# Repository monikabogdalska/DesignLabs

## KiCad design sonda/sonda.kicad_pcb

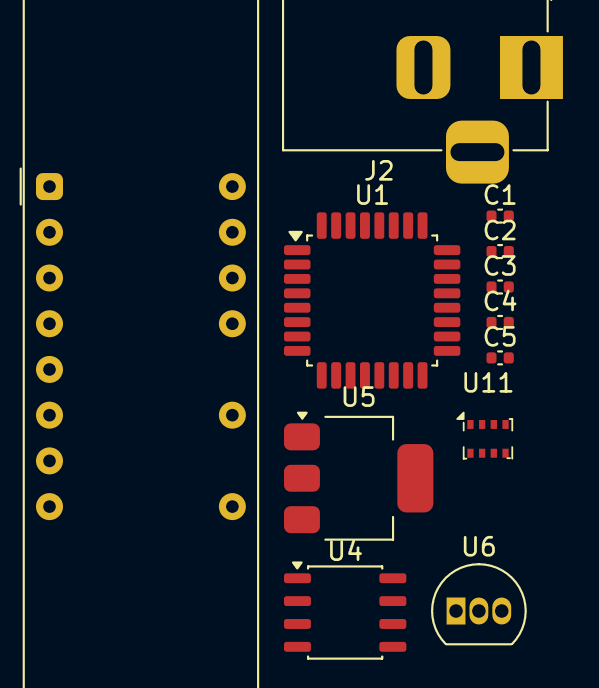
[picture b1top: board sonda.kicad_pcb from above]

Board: 2 copper layers, 12 parts (0 on the bottom side), 22 nets, no tracks yet.

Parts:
C1, C2, C3, C4, C5: 100nF; C_0402_1005Metric
J2: Jack-DC; BarrelJack_Horizontal
U1: ATmega328PB-A; TQFP-32_7x7mm_P0.8mm
U3: LTC-4627JD; LTC-4627Jx
U4: CH340N; JEITA_SOIC-8_3.9x4.9mm_P1.27mm
U5: AMS1117-3.3; SOT-223-3_TabPin2
U6: DS18B20; TO-92_Inline
U11: BMP280; Bosch_LGA-8_2x2.5mm_P0.65mm_ClockwisePinNumbering

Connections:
+3.3V: C1.1, C2.1, C4.1, C5.1, U1.4 (VCC), U3.1 (VCC), U4.5 (VCC), U5.2 (VO), U6.3 (V_{DD}), U11.8 (VDD)
+5V: C3.1, J2.1, U5.3 (VI)
GND: C1.2, C2.2, C3.2, C4.2, C5.2, J2.2, U1.5 (GND), U1.21 (GND), U4.3 (GND), U5.1 (GND), U6.1 (GND), U11.1 (GND), U11.7 (GND)
unnamed: U1.12 (PB0), U3.15 (G)
unnamed: U1.13 (PB1), U3.7 (DP)
unnamed: U1.14 (PB2), U11.2 (CSB)
unnamed: U1.15 (PB3), U11.5 (SDO)
unnamed: U1.16 (PB4), U11.3 (SDI)
unnamed: U1.17 (PB5), U11.4 (SCK)
unnamed: U1.23 (PC0), U3.2 (D1)
unnamed: U1.24 (PC1), U3.6 (D2)
unnamed: U1.25 (PC2), U3.8 (D3)
unnamed: U1.26 (PC3), U3.4 (D4)
unnamed: U1.30 (PD0), U4.6 (TXD)
unnamed: U1.31 (PD1), U4.7 (RXD)
unnamed: U1.32 (PD2), U6.2 (DQ)
unnamed: U1.1 (PD3), U3.16 (B)
unnamed: U1.2 (PD4), U3.13 (C)
unnamed: U1.9 (PD5), U3.3 (D)
unnamed: U1.10 (PD6), U3.5 (E)
unnamed: U1.11 (PD7), U3.11 (F)
unnamed: U1.7 (XTAL1/PB6), U3.14 (A)

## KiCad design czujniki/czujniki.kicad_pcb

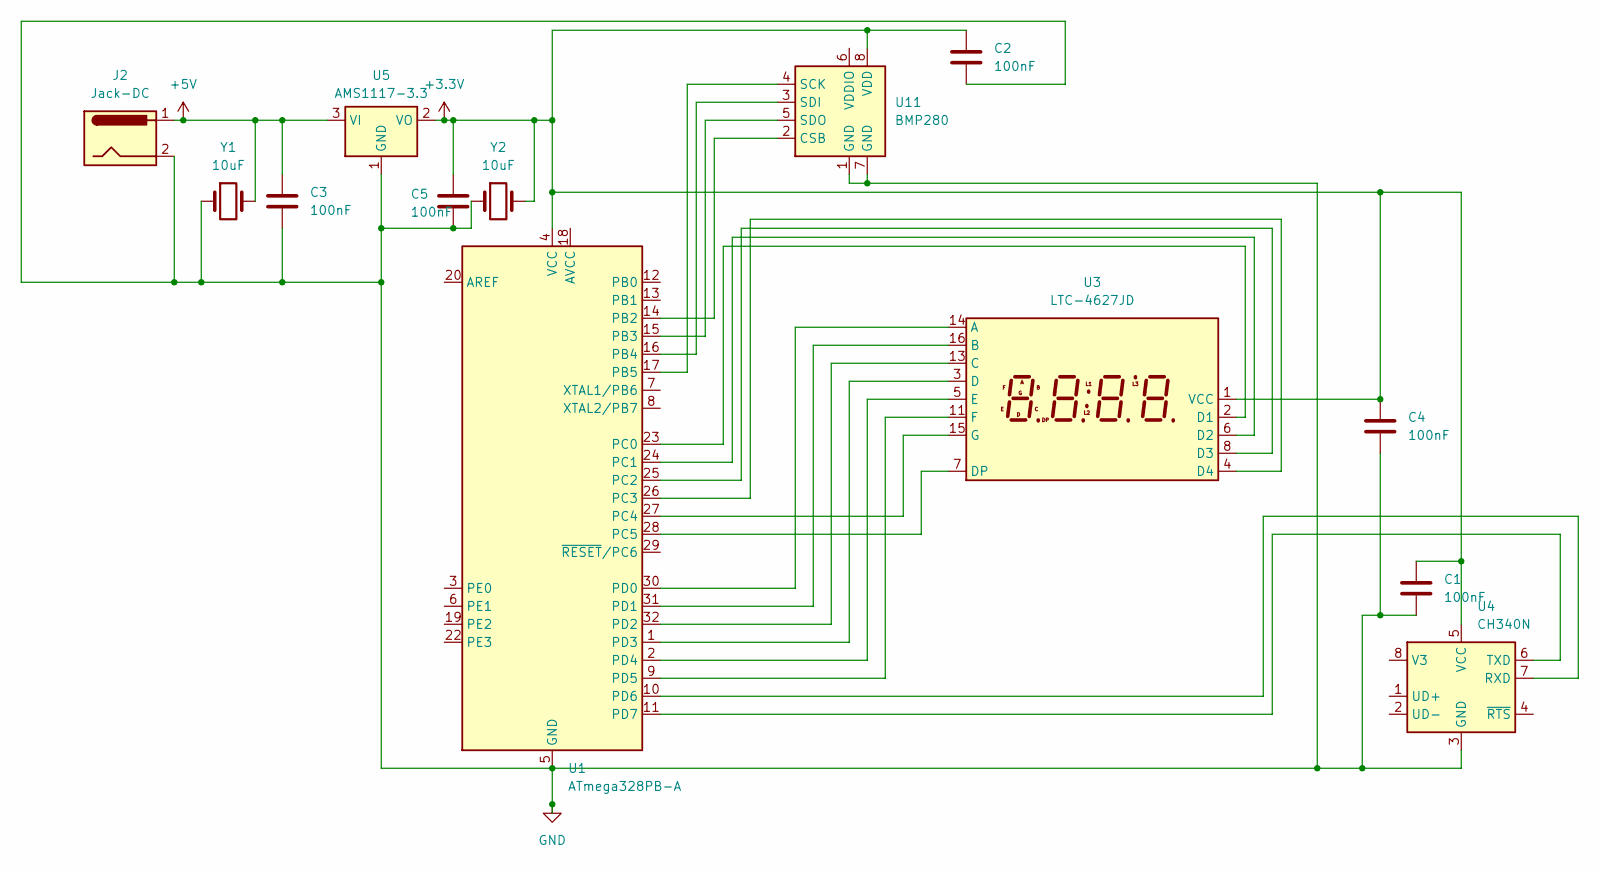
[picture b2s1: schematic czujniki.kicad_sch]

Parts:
C1, C2, C3, C4, C5: 100nF; C_0402_1005Metric
J2: Jack-DC; BarrelJack_Horizontal
U1: ATmega328PB-A; TQFP-32_7x7mm_P0.8mm
U3: LTC-4627JD; LTC-4627Jx
U4: CH340N; JEITA_SOIC-8_3.9x4.9mm_P1.27mm
U5: AMS1117-3.3; SOT-223-3_TabPin2
U11: BMP280; Bosch_LGA-8_2x2.5mm_P0.65mm_ClockwisePinNumbering
Y1, Y2: 10uF; CP_Elec_6.3x7.7

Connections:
+3.3V: C1.1, C2.1, C4.1, C5.1, U1.4 (VCC), U3.1 (VCC), U4.5 (VCC), U5.2 (VO), U11.8 (VDD), Y2.2
+5V: C3.1, J2.1, U5.3 (VI), Y1.2
GND: C1.2, C2.2, C3.2, C4.2, C5.2, J2.2, U1.5 (GND), U1.21 (GND), U4.3 (GND), U5.1 (GND), U11.1 (GND), U11.7 (GND), Y1.1, Y2.1
unnamed: U1.14 (PB2), U11.2 (CSB)
unnamed: U1.15 (PB3), U11.5 (SDO)
unnamed: U1.16 (PB4), U11.3 (SDI)
unnamed: U1.17 (PB5), U11.4 (SCK)
unnamed: U1.23 (PC0), U3.2 (D1)
unnamed: U1.24 (PC1), U3.6 (D2)
unnamed: U1.25 (PC2), U3.8 (D3)
unnamed: U1.26 (PC3), U3.4 (D4)
unnamed: U1.27 (PC4), U3.15 (G)
unnamed: U1.28 (PC5), U3.7 (DP)
unnamed: U1.30 (PD0), U3.14 (A)
unnamed: U1.31 (PD1), U3.16 (B)
unnamed: U1.32 (PD2), U3.13 (C)
unnamed: U1.1 (PD3), U3.3 (D)
unnamed: U1.2 (PD4), U3.5 (E)
unnamed: U1.9 (PD5), U3.11 (F)
unnamed: U1.10 (PD6), U4.7 (RXD)
unnamed: U1.11 (PD7), U4.6 (TXD)

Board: 2 copper layers, 13 parts (0 on the bottom side), 21 nets, no tracks yet.

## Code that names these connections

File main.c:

#define F_CPU 16000000UL
#include <avr/io.h>
#include <util/delay.h>
#include <avr/interrupt.h>
#include <avr/pgmspace.h>
#include <stdio.h>
#include <string.h>

#include "usart.h"
#include "i2c.h"
#include "bmp280.h"
#include "ds18b20.h" 
#include "onewire.h"

// ZMIENNA VOLATILE - Konieczna dla zmiennych edytowanych w przerwaniu
volatile uint8_t flaga_pomiaru = 0;
volatile int liczba = 0;

int kod1, kod2;
int16_t temp_raw; 

int alfabet(char znak)
{
    switch (znak)
    {
        case '1': kod1 = 0b11001111; kod2 = 0b11111111; break;
        case '2': kod1 = 0b00100111; kod2 = 0b11111101; break;
        case '3': kod1 = 0b10000111; kod2 = 0b11111101; break;
        case '4': kod1 = 0b11001111; kod2 = 0b11111100; break;
        case '5': kod1 = 0b10010111; kod2 = 0b11111100; break;
        case '6': kod1 = 0b00010111; kod2 = 0b11111100; break;
        case '7': kod1 = 0b11000111; kod2 = 0b11111111; break;
        case '8': kod1 = 0b00000111; kod2 = 0b11111100; break;
        case '9': kod1 = 0b10000111; kod2 = 0b11111100; break;
        case '0': kod1 = 0b00000111; kod2 = 0b11111110; break;
        default:  kod1 = 0xFF;       kod2 = 0b11111111; break;
    }
    return kod1;
}

void seg7_init()
{
    DDRB |= (1 << PB0) | (1 << PB1);
    DDRD |= (1 << PD3) | (1 << PD4) | (1 << PD5) | (1 << PD6) | (1 << PD7);
    DDRC |= (1 << PC0) | (1 << PC1) | (1 << PC2) | (1 << PC3);
}

void display(char znak, int index)
{
    
    // 2. Ustaw segmenty
    alfabet(znak);
    PORTB = kod2;
    PORTD = kod1;
    
    // 3. W³¹cz konkretny wywietlacz
    PORTC = index; 
    
    // 4. Krótkie opónienie dla oka
    _delay_ms(2); // 4ms * 4 cyfry = 16ms (ok. 60Hz odwie¿ania)
}

void timer_init()
{
    TCCR1B |= (1 << WGM12);   // CTC mode
    TCCR1B |= (1 << CS12) | (1 << CS10);  // Preskaler 1024
    OCR1A = 7812;  // Przerwanie co ok 0.5s
    TIMSK1 |= (1 << OCIE1A);
}

// PRZERWANIE 
ISR(TIMER1_COMPA_vect)
{
    flaga_pomiaru = 1; // dajemy sygna³ do pomiarów
}

void wykonaj_pomiary() {
    float temp = bmp280_read_temperature();
    float press = bmp280_read_pressure();

    uart_puts("Temp: ");
    uart_putfloat(temp);
    uart_puts(" C\r\n");

    uart_puts("Press: ");
    uart_putfloat(press);
    uart_puts(" Pa\r\n\r\n");
    
    // Aktualizacja liczby na wywietlacz
    

 
    if(ds18b20_read_temp(&temp_raw))
    {
        float tempC = temp_raw / 16.0;
        uart_putfloat(tempC);
        uart_puts("\r\n");
		liczba = (int)tempC;
	}
	
    else
    {
        uart_puts("Blad DS18B20\r\n");
    }
    
}

int main(void)
{   
    I2C_init();
    bmp280_init();
    
    uart_init(BAUD_CALC(115200));
    stdout = &uart0_io;
    stdin = &uart0_io;
    
    seg7_init();
    timer_init();
    
    sei(); // W³¹czamy przerwania
    
    printf("System start\n");

    while(1)
    {
        // 1. Sprawd czy czas na pomiar (co 0.5s)
        if (flaga_pomiaru == 1) {
            wykonaj_pomiary(); // To zajmie chwilê, wywietlacz mo¿e mrugn¹æ
            flaga_pomiaru = 0; // Kasujemy flagê
        }

        // 2. Obs³uga wywietlacza (musi dzia³aæ non-stop)
        char tysiace = liczba / 1000;
        char setki = (liczba / 100) % 10;
        char dziesiatki = (liczba / 10) % 10;
        char jednosci = liczba % 10;
        
        display(tysiace + '0', 0b11111110);
        display(setki + '0',   0b11111101);
        display(dziesiatki + '0', 0b11111011);
        display(jednosci + '0',   0b11110111);
    }
}

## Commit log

2025-11-05 Create Kod_wysw_7segm_czytnik_kart
2025-11-05 Add files via upload
    Mikrokontroler AtMega328 połączony z wyświetlaczem 7 segmentowym LTC4627JD oraz czytnikiem kart BMP280. Wyjścia zostały sprawdzone z notami katalogowymi zamieszczonymi również tutaj na githubie.
2025-11-05 Rename image.png to 7segm_czytnik.png
2025-11-05 atmega_led.png
2025-11-19 Rename image.png to uart.png
2025-11-19 Rename image.png to usb_uart.png
2025-11-19 Rename image.png to ams_jako_stabilizator.png
2025-11-20 Rename image.png to wyglad_pcb.png
2025-11-20 Create UART_bez_biblio
    Trzeba dodać biblioteki bo nie zadziala
2025-11-20 Rename image.png to uart_dziala.png
2025-12-04 Rename image.png to sonda.png
2025-12-18 Add files via upload
    Komplet kod
2025-12-18 Rename image.png to schemat_projekt_final.png
2025-12-18 Rename image.png to pcb_projekt.png
2026-01-21 Create temp
2026-01-22 Commit changes
2026-01-22 Rename 7eab448e-54d3-48d9-bf91-038540a4d2f9.jpg to High
2026-01-22 Rename 9a3f095f-5fab-4f8c-a124-f8614e6e9c63.jpg to Stable
2026-01-22 Rename e98cc7b4-fcdb-4942-be2e-54060f0ccb6c.jpg to Low
2026-01-22 Create Report
2026-01-22 Rename Design lab (1).docx to Design lab.docx
